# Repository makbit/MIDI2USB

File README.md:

# MIDI2USB - Free and improved MIDI to USB Converter (v.1.3 Nov 2022)

This device is designed to connect various musical instruments to a PC via the USB Fullspeed port. This is an improved version of the chinese **USB2MIDI** adapter in the same case. There are: 1 IN port, 1 OUT port, 16 channels/instruments, Plug-and-Play feature, Build-in drivers. The adapter is compatible with Windows (32-bit, 64-bit) and was tested with MIDI-OX, MuseScore, Cubase, etc.

The device is based on Silicon Laboratories 8-bit 8051 MCU [EFM8UB20F32](https://www.silabs.com/mcu/8-bit/efm8-universal-bee/device.efm8ub20f32g-qfp32), (avg. price $2). This MCU has Fullspeed USB controller and adjustable internal oscillator (0.25%). You can use any compatible MCU, for example [C8051F380](https://www.silabs.com/mcu/8-bit/c8051f38x/device.c8051f380-gq).

### Advantages of this MIDI2USB adapter:
* Open and clean source code with comments;
* Compliant to hardware and software [MIDI Specification 1.0](https://www.midi.org/specifications-old/item/the-midi-1-0-specification);
* All electronic components are available in your local shop;
* I use it myself.
* MIT License

The [`Hardware`](Hardware) folder contains Eagle CAD 9.0 schematics files, board file and component library. The .BRD file can be sent to your favourite PCB manufacturer. The board schematics can be found in the[`Hardware/Efm8Midi.png`](Hardware/Efm8Midi.png) file.

In the [`Firmware`](Firmware) folder you will find all C-source files for this project. Files from SiLabs SDK are located in the EFM8 subfolder. The project was developed with the [IAR Embedded Workbench IDE 8051](https://www.iar.com/iar-embedded-workbench/#!?architecture=8051). I beleive the source code is compatible with the [Keil uVision PK51](https://www.keil.com/c51/pk51kit.asp).

### Some pictures of this MIDI2USB converter :cool:

### TODO :pen:
- [x] Switch to UART#1 with FIFO buffer (done);
- [x] Test and improve SysEx handler (done);
- [x] Added Real-Time Message handler (done/test required);
- [ ] Move all components to one side;
- [ ] Add 4-pin header to optionaly solder USB cable;
- [ ] Find a sponsor :smile:

[GitHub readme tips&tricks](https://help.github.com/articles/basic-writing-and-formatting-syntax/)

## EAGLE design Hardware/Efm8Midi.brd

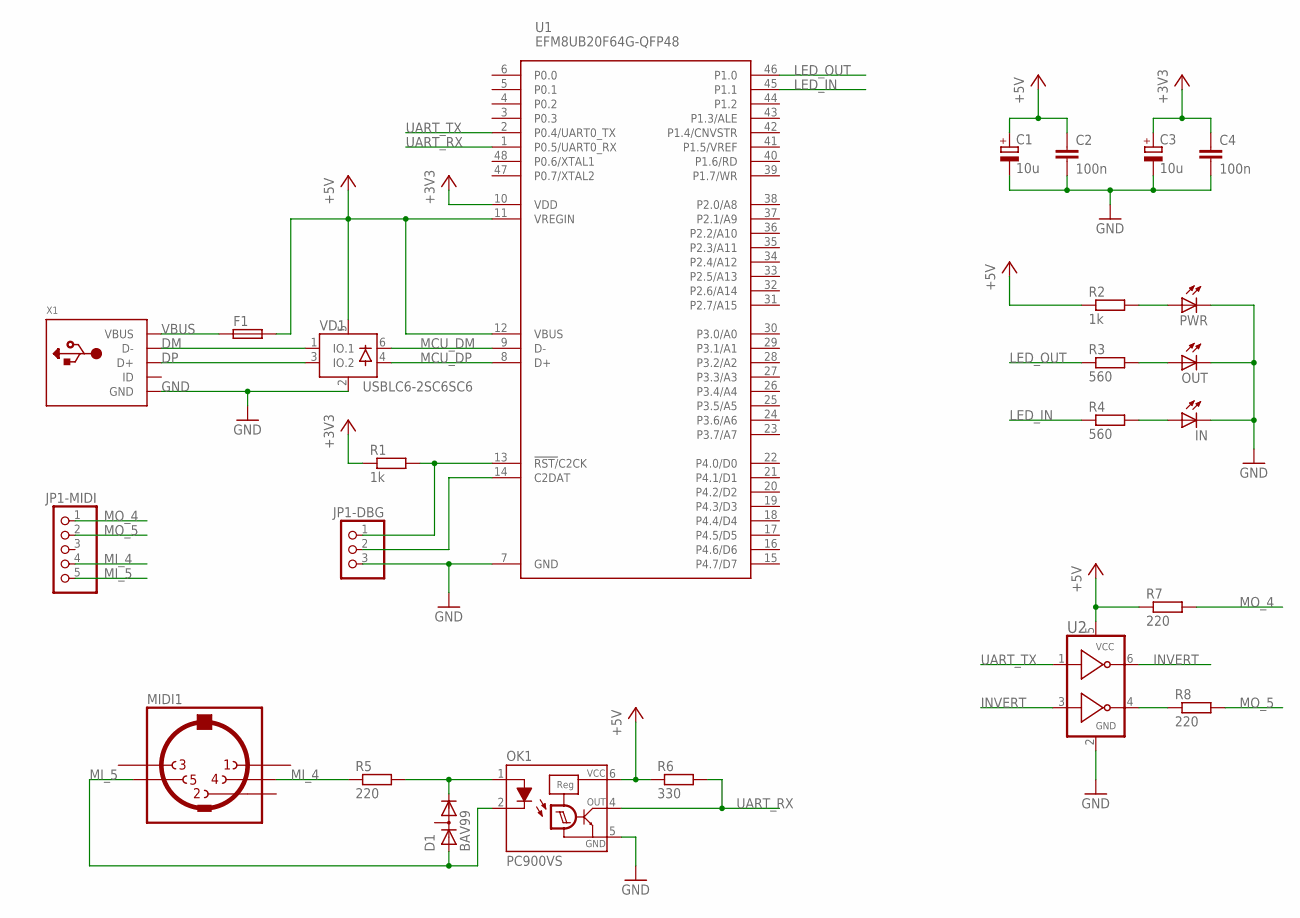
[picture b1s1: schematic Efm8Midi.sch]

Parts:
C1, C3: 10u; CT3216
C2, C4: 100n; C1206
D1: BAV99; SOT23
F1: MF-NSMF; RCL-1206
IN: LED3MM
JP1-DBG: PINHD-1X3; 1X03
JP1-MIDI: PINHD-1X5; 1X05
MIDI1: MIDIJACK; MIDI-CP-2350
OK1: PC900VS; DIL6-SMD
OUT: LED3MM
PWR: LED3MM
R1, R2: 1k; R0805
R3, R4: 560; R0805
R5, R7, R8: 220; R0805
R6: 330; R0805
U1: EFM8UB20F64G-QFP48; QFP48-7X7-0P5MM
U2: 74LVC2G04SOT-23-6-DBV; SOT-23-290X160-DBV
VD1: USBLC6-2SC6SC6; SOT-23-6L
X1: MINI-USB-B32005-301; USB-MINI-B

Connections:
+3V3: C3.+, C4.1, R1.1, U1.10 (VDD)
+5V: C1.+, C2.1, F1.2, OK1.6 (VCC), R2.1, R6.1, R7.1, U1.11 (VREGIN), U1.12 (VBUS), U2.5 (VCC), VD1.5 (VBUS)
DM: VD1.1 (IO.1), X1.D-
DP: VD1.3 (IO.2), X1.D+
GND: C1.-, C2.2, C3.-, C4.2, IN.K (C), JP1-DBG.3, OK1.5 (GND), OUT.K (C), PWR.K (C), U1.7 (GND), U2.2 (GND), VD1.2 (GND), X1.GND
INVERT: U2.3 (A2), U2.6 (Y1)
LED_IN: R4.1, U1.45 (P1.1)
LED_OUT: R3.1, U1.46 (P1.0)
MCU_DM: U1.9 (D-), VD1.6 (IO_1)
MCU_DP: U1.8 (D+), VD1.4 (IO_2)
MI_4: JP1-MIDI.4, MIDI1.4, R5.1
MI_5: D1.1 (A), JP1-MIDI.5, MIDI1.5, OK1.2 (C)
MO_4: JP1-MIDI.1, R7.2
MO_5: JP1-MIDI.2, R8.2
unnamed: IN.A, R4.2
unnamed: JP1-DBG.1, R1.2, U1.13 (!RST/!C2CK)
unnamed: PWR.A, R2.2
unnamed: R8.1, U2.4 (Y2)
unnamed: D1.2 (C), OK1.1 (A), R5.2
unnamed: JP1-DBG.2, U1.14 (C2DAT)
unnamed: OUT.A, R3.2
UART_RX: OK1.4 (OUT), R6.2, U1.1 (P0.5/UART0_RX)
UART_TX: U1.2 (P0.4/UART0_TX), U2.1 (A1)
VBUS: F1.1, X1.VBUS

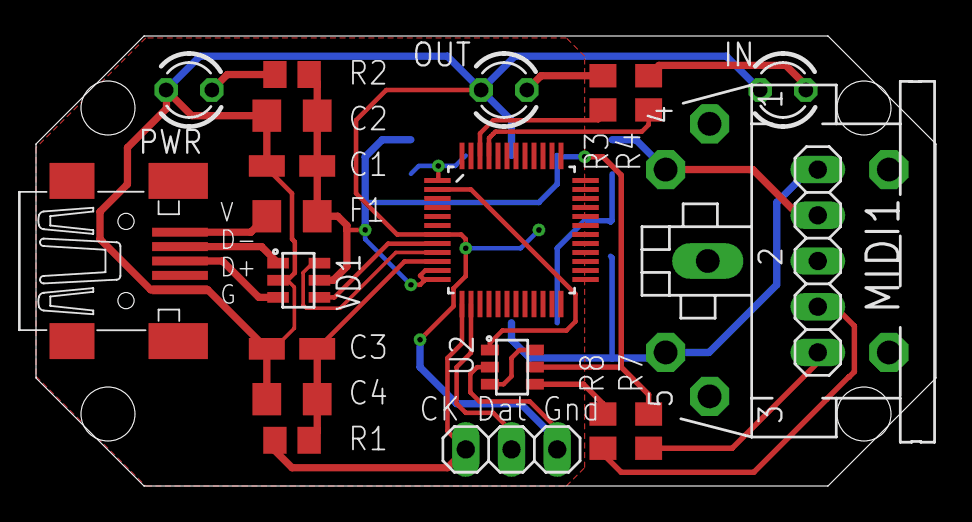
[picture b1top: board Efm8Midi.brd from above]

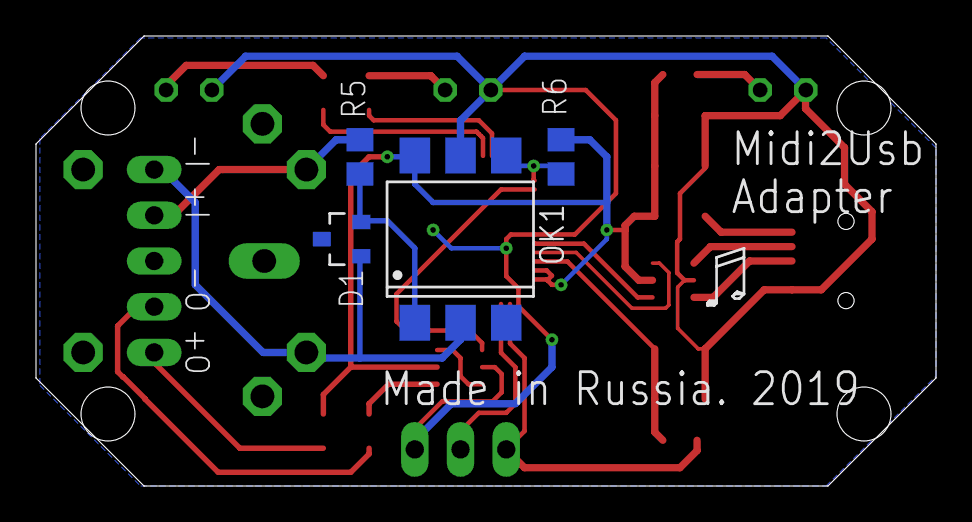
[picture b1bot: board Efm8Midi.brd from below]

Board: 2 copper layers, 50.0 x 25.0 mm, 25 parts (4 on the bottom side), 24 nets.

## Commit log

2020-08-20 Device images
2020-08-20 Version 0.2 (August 2020)
2020-08-20 Version 0.2 (August 2020)
    Spaces/Tabs fix
2020-08-21 Put images into separate folder
2020-08-21 Update link to images, and some formatting
2021-09-27 Edit version number (2021.09.25)
2021-09-27 Edit version number (2021.09.16)
2021-09-27 No more magic constants + UART1 (2021.09.25)
2021-09-27 Now we use UART1 with FIFO (2021.09.25)
2021-09-27 SysEx support and UART1 with FIFO (2021.09.25)
2021-09-27 Firmware (hex format), v.1.2 (September 2021)
2022-11-16 Add files via upload
    Version number update after fix
2022-11-16 Added Real-Time Message handler
2022-11-16 Version 1.3 with MIDI Real-Time Message handler
2022-11-16 Version 1.3 with Real-Time Message handler.
